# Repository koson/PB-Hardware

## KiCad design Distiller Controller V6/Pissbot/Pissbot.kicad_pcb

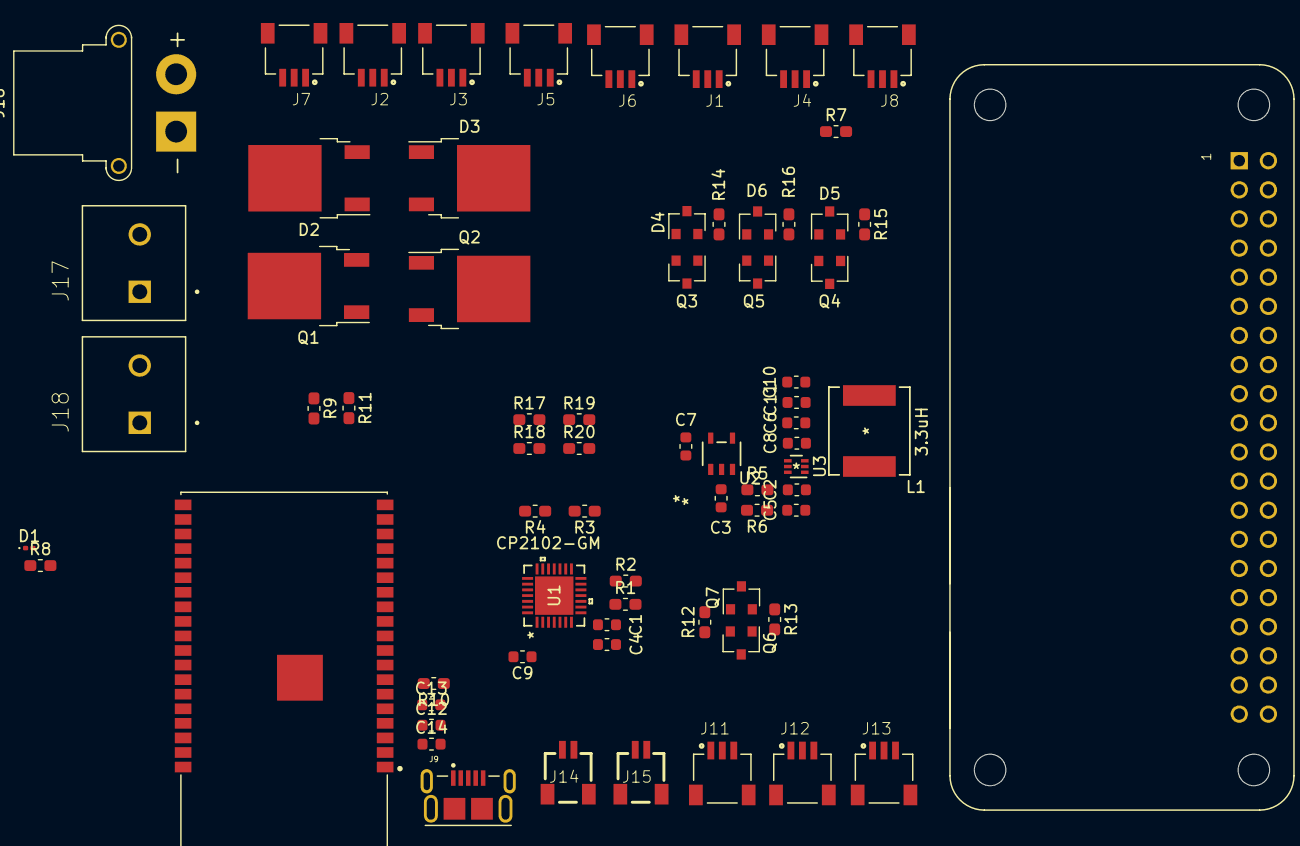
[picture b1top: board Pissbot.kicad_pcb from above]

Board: 4 copper layers, 70 parts (0 on the bottom side), 51 nets, no tracks yet.

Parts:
A1: ESP32-WROVER-I; XCVR_ESP32-WROVER-I
C1: 4.7uF; C_0603_1608Metric
C2, C5, C6: 10uF; C_0603_1608Metric
C3, C7: 1uF; C_0603_1608Metric
C4, C8, C11, C13, C14: 0.1uF; C_0603_1608Metric
C9, C10, C12: 22uF; C_0603_1608Metric
D1: LED_Small; LED_0201_0603Metric
D2, D3: MBRD835TR; TO-252-2
D4, D5, D6: 9.1V; SOT-23
J1: T1; JST_SM03B-SRSS-TB(LF)(SN)
J2: T5; JST_SM03B-SRSS-TB(LF)(SN)
J3: T2; JST_SM03B-SRSS-TB(LF)(SN)
J4: T6; JST_SM03B-SRSS-TB(LF)(SN)
J5: T3; JST_SM03B-SRSS-TB(LF)(SN)
J6: T7; JST_SM03B-SRSS-TB(LF)(SN)
J7, J11, J12, J13: T4; JST_SM03B-SRSS-TB(LF)(SN)
J8: T8; JST_SM03B-SRSS-TB(LF)(SN)
J9: MicroUSB_ESP; Micro-USB-TE_2040002-1
J10: Raspberry_Pi_2_3; ADA3708_RPI-ZERO
J14, J15: SM02B-SRSS-TB(LF)(SN)
J16: Conn_01x02_Female; AMASS_XT30PW-F_1x02_P2.50mm_Horizontal
J17, J18: Conn_01x02_Female; CUI_TB001-500-02BE
L1: 3.3uH; ECS-MPIL0630-3R3MC
Q1, Q2: MCU80N03A-TP; TO-252-2
Q3, Q4, Q5: SSM3J338R; SOT-23
Q6, Q7: S8050; SOT-23
R1: 22.1k; R_0603_1608Metric_Pad1.05x0.95mm_HandSolder
R2: 47.5k; R_0603_1608Metric_Pad1.05x0.95mm_HandSolder
R3, R7, R17, R18, R19, R20: 2k; R_0603_1608Metric_Pad1.05x0.95mm_HandSolder
R4, R6, R10, R12, R13: 10k; R_0603_1608Metric_Pad1.05x0.95mm_HandSolder
R5: 73.2k; R_0603_1608Metric_Pad1.05x0.95mm_HandSolder
R8: 1k; R_0603_1608Metric_Pad1.05x0.95mm_HandSolder
R9, R11: 4.7k; R_0603_1608Metric_Pad1.05x0.95mm_HandSolder
R14, R15, R16: 100k; R_0603_1608Metric_Pad1.05x0.95mm_HandSolder
U1: CP2102-GM
U2: TLV74033PDBVR
U3: TPS563231DRLR

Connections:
1WIRE: A1.33, J1.2, J2.2, J3.2, J4.2, J5.2, J6.2, J7.2, J8.2, R7.1
3.3V: A1.2, C12.1, C14.1, J1.1, J2.1, J3.1, J4.1, J5.1, J6.1, J7.1, J8.1, R7.2, R10.1
12V: D2.1, D3.1
+3V3: C7.1, J11.3, J12.3, J13.3, R3.2, R17.1, R18.1, U2.5
+5V: C3.1, D4.1, D5.1, D6.1, J10.2, J10.4, Q3.2, Q4.2, Q5.2, R1.2, U2.1, U2.3
+12V: C2.1, C5.1, C6.1, J16.1, J17.1, J18.1, U3.1, U3.5
/5V_IN: C9.1, C10.1, C11.1, L1.2, Q5.3, R5.1, R8.1
/DTR: Q7.1, R12.2, U1.28
/ELEMEMENT_1: J15.2, R20.1
/ELEMENT_2: J14.2, R19.1
/ESP_VBUS: J9.1, Q4.3
/FAN: A1.11, J13.2
/IO0: A1.25, Q7.3
/PRODUCT_FLOW: A1.4, J12.1, R18.2
/REFLUX_FLOW: A1.5, J11.1, R17.2
/RTS: Q6.1, R13.2, U1.24
/UART1_RX: A1.7, J10.8
/UART1_TX: A1.10, J10.10
/USB_D+: J9.3, U1.5
/USB_D-: J9.2, U1.4
EN: A1.3, C13.1, Q6.3, R10.2
GND: C1.2, C2.2, C3.2, C4.2, C5.2, C6.2, C7.2, C9.2, C10.2, C11.2, C12.2, C13.2, C14.2, D1.1, J1.3, J2.3, J3.3, J4.3, J5.3, J6.3, J7.3, J8.3, J9.5, J10.6, J10.9, J10.14, J10.20, J10.25, J10.30, J10.34, J10.39, J11.2, J12.2, J13.1, J14.1, J15.1, J16.2, Q1.3, Q2.3, R2.2, R4.2, R6.2, R9.2, R11.2, R14.1, R15.1, R16.1, R19.2, R20.2, U1.3, U1.29, U2.2, U3.3
unnamed: A1.1, A1.15, A1.38
unnamed: C1.1, C4.1, U1.6, U1.7
unnamed: C8.1, U3.4
unnamed: C8.2, L1.1, U3.2
unnamed: D1.2, R8.2
unnamed: D4.2, Q3.1, R14.2
unnamed: D5.2, Q4.1, R15.2
unnamed: D6.2, Q5.1, R16.2
unnamed: J1.S1, J1.S2
unnamed: J2.S1, J2.S2
unnamed: J3.S1, J3.S2
unnamed: J4.S1, J4.S2
unnamed: J5.S1, J5.S2
unnamed: J6.S1, J6.S2
unnamed: J7.S1, J7.S2
unnamed: J8.S1, J8.S2
unnamed: J11.S1, J11.S2
unnamed: J12.S1, J12.S2
unnamed: J13.S1, J13.S2
unnamed: Q6.2, R12.1
unnamed: Q7.2, R13.1
unnamed: R1.1, R2.1, U1.8
unnamed: R3.1, U1.9
unnamed: R4.1, U1.11
unnamed: R5.2, R6.1, U3.6
P1_LOAD: D2.2, J17.2, Q1.2
P2_LOAD: D3.2, J18.2, Q2.2
PROD-PUMP: Q1.1, R9.1
REFLUX-PUMP: Q2.1, R11.1

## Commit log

2020-10-26 Updated PCB
2020-11-22 Updated PCB. Added library files
2022-02-16 Save
2022-08-18 test

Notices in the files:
parts and their libraries:
Copyright 2016 Accelerated Designs. All rights reserved.
